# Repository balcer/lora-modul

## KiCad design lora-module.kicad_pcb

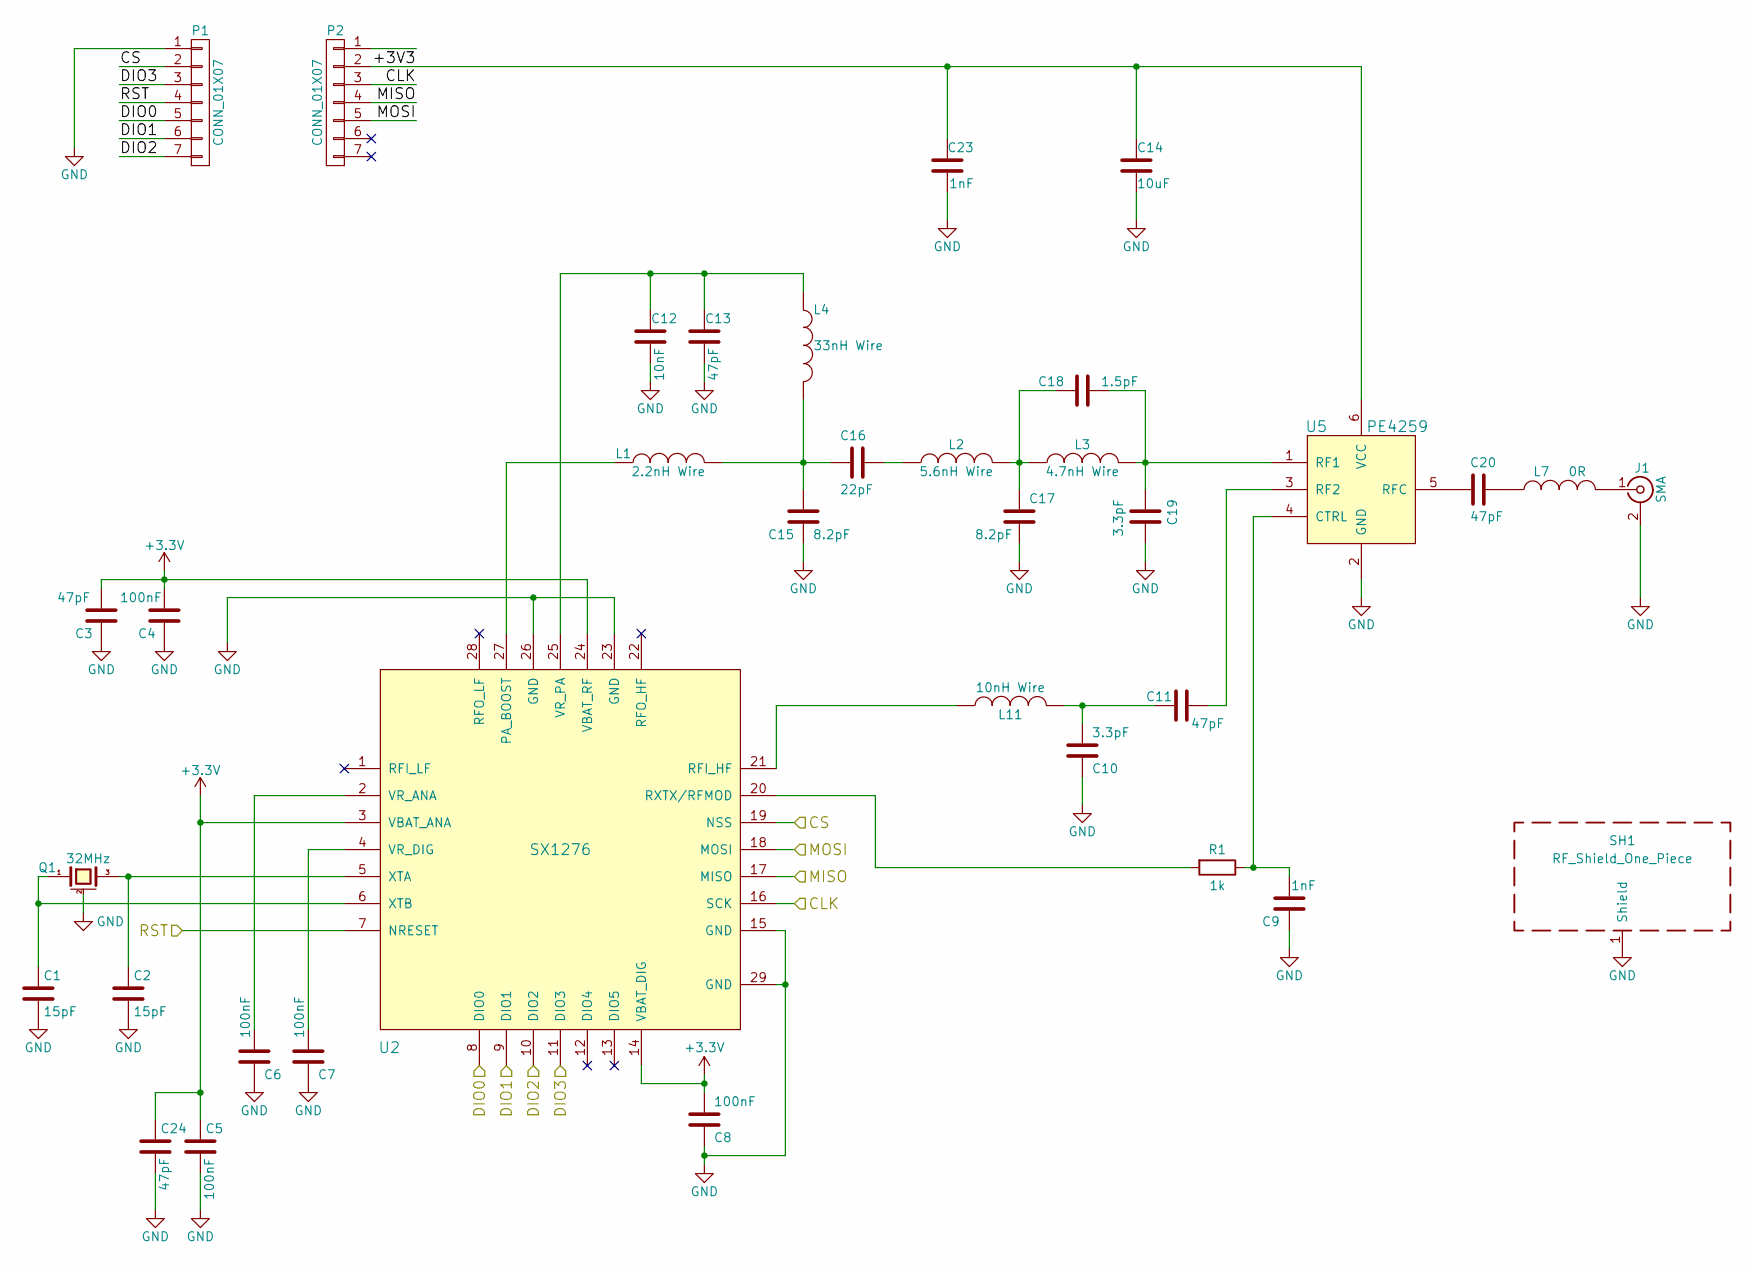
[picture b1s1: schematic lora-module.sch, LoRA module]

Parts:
C1, C2: 15pF; C_0402
C3, C11, C13, C20, C24: 47pF; C_0402
C4, C5, C6, C7, C8: 100nF; C_0402
C9, C23: 1nF; C_0402
C10, C19: 3.3pF; C_0402
C12: 10nF; C_0402
C14: 10uF; C_0805
C15, C17: 8.2pF; C_0402
C16: 22pF; C_0402
C18: 1.5pF; C_0402
J1: SMA; SMA-16
L1: 2.2nH Wire; L_0402
L2: 5.6nH Wire; L_0402
L3: 4.7nH Wire; L_0402
L4: 33nH Wire; L_0402
L7: 0R; L_0402
L11: 10nH Wire; L_0402
P1, P2: CONN_01X07; Pin_Header_Straight_1x07_Pitch2.54mm
Q1: 32MHz; Crystal_SMD_EuroQuartz_MT-4pin_3.2x2.5mm
R1: 1k; R_0402
SH1: RF_Shield_One_Piece; inAIR9B_shield
U2: SX1276; QFN-28-1EP_6x6mm_Pitch0.65mm
U5: PE4259; SOT-363_SC-70-6

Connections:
/CLK: P2.3, U2.16 (SCK)
/CS: P1.2, U2.19 (NSS)
/DIO0: P1.5, U2.8 (DIO0)
/DIO1: P1.6, U2.9 (DIO1)
/DIO2: P1.7, U2.10 (DIO2)
/DIO3: P1.3, U2.11 (DIO3)
/MISO: P2.4, U2.17 (MISO)
/MOSI: P2.5, U2.18 (MOSI)
/RST: P1.4, U2.7 (NRESET)
GND: C1.2, C2.2, C3.2, C4.2, C5.2, C6.2, C7.2, C8.2, C9.1, C10.2, C12.2, C13.2, C14.2, C15.2, C17.2, C19.1, C23.1, C24.2, J1.2 (Ext), P1.1, Q1.2 (case), SH1.1, U2.15 (GND), U2.23 (GND), U2.26 (GND), U2.29 (GND), U5.2 (GND)
unnamed: C1.1, Q1.1, U2.6 (XTB)
unnamed: C2.1, Q1.3, U2.5 (XTA)
unnamed: C6.1, U2.2 (VR_ANA)
unnamed: C7.1, U2.4 (VR_DIG)
unnamed: C9.2, R1.1, U5.4 (CTRL)
unnamed: C10.1, C11.2, L11.2
unnamed: C11.1, U5.3 (RF2)
unnamed: C12.1, C13.1, L4.1, U2.25 (VR_PA)
unnamed: C15.1, C16.2, L1.2, L4.2
unnamed: C16.1, L2.1
unnamed: C17.1, C18.2, L2.2, L3.1
unnamed: C18.1, C19.2, L3.2, U5.1 (RF1)
unnamed: C20.1, L7.1
unnamed: C20.2, U5.5 (RFC)
unnamed: J1.1 (In), L7.2
unnamed: L1.1, U2.27 (PA_BOOST)
unnamed: L11.1, U2.21 (RFI_HF)
unnamed: R1.2, U2.20 (RXTX/RFMOD)

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
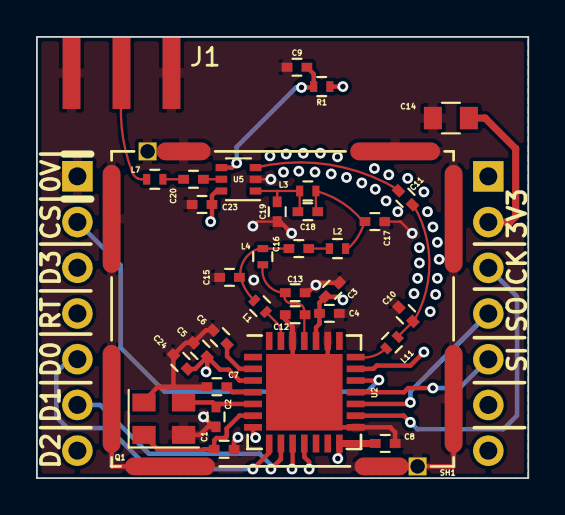
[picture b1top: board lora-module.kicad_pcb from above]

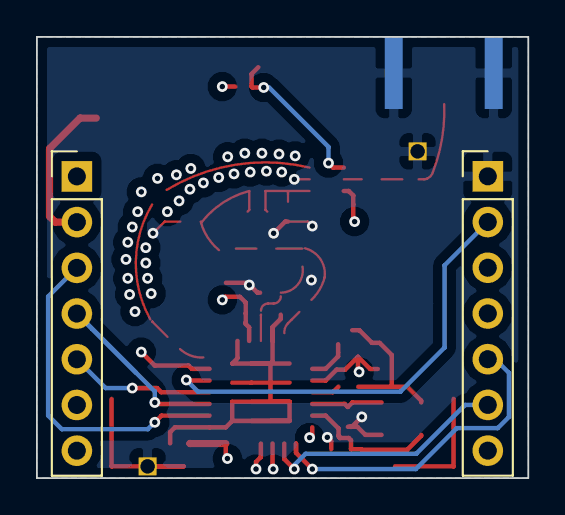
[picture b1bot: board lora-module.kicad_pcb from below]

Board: 4 copper layers, 27.3 x 24.5 mm, 36 parts (2 on the bottom side), 29 nets.

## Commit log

2017-08-15 repo start
2017-08-15 added most of components to PCB
2017-10-01 added all components description
2017-10-01 added PCB stack values
2017-10-01 added poligones for all layers
2017-10-01 added first Cu arc track for RF signal
2017-10-01 added RF design specification
2017-10-01 added arcs as RF tracks
2017-10-01 removed 2 caps, added routing
2017-10-01 added all traces and fix top poligon
2017-10-02 schematic simplified
2017-10-02 added 3d packsge for RF switch
